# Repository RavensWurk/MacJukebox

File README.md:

This project is an effort to develop a jukebox expansion board for vintage Macintosh computers. 
It is meant to plug into the standard modem port on all compacts (and later desktops), and provide
USB storage, audio output via a headphone jack, and a control interface for the computers. 

It will support MP3 files at most common bitrates and sample frequencies. The Macintosh, being
unable to actually decode modern music files or output high qualithy sound, will act as the command
and control interface for this external board. Playlists can be made, viewing artists/albums/songs, 
controlling mixer levels and volume, and the external board will handle all the decoding of the file,
outputting it to the audio jack.

This repo is organised in to two parts, the firmware for the board itself under "Board", and the Macintosh
software side under "MacApp".

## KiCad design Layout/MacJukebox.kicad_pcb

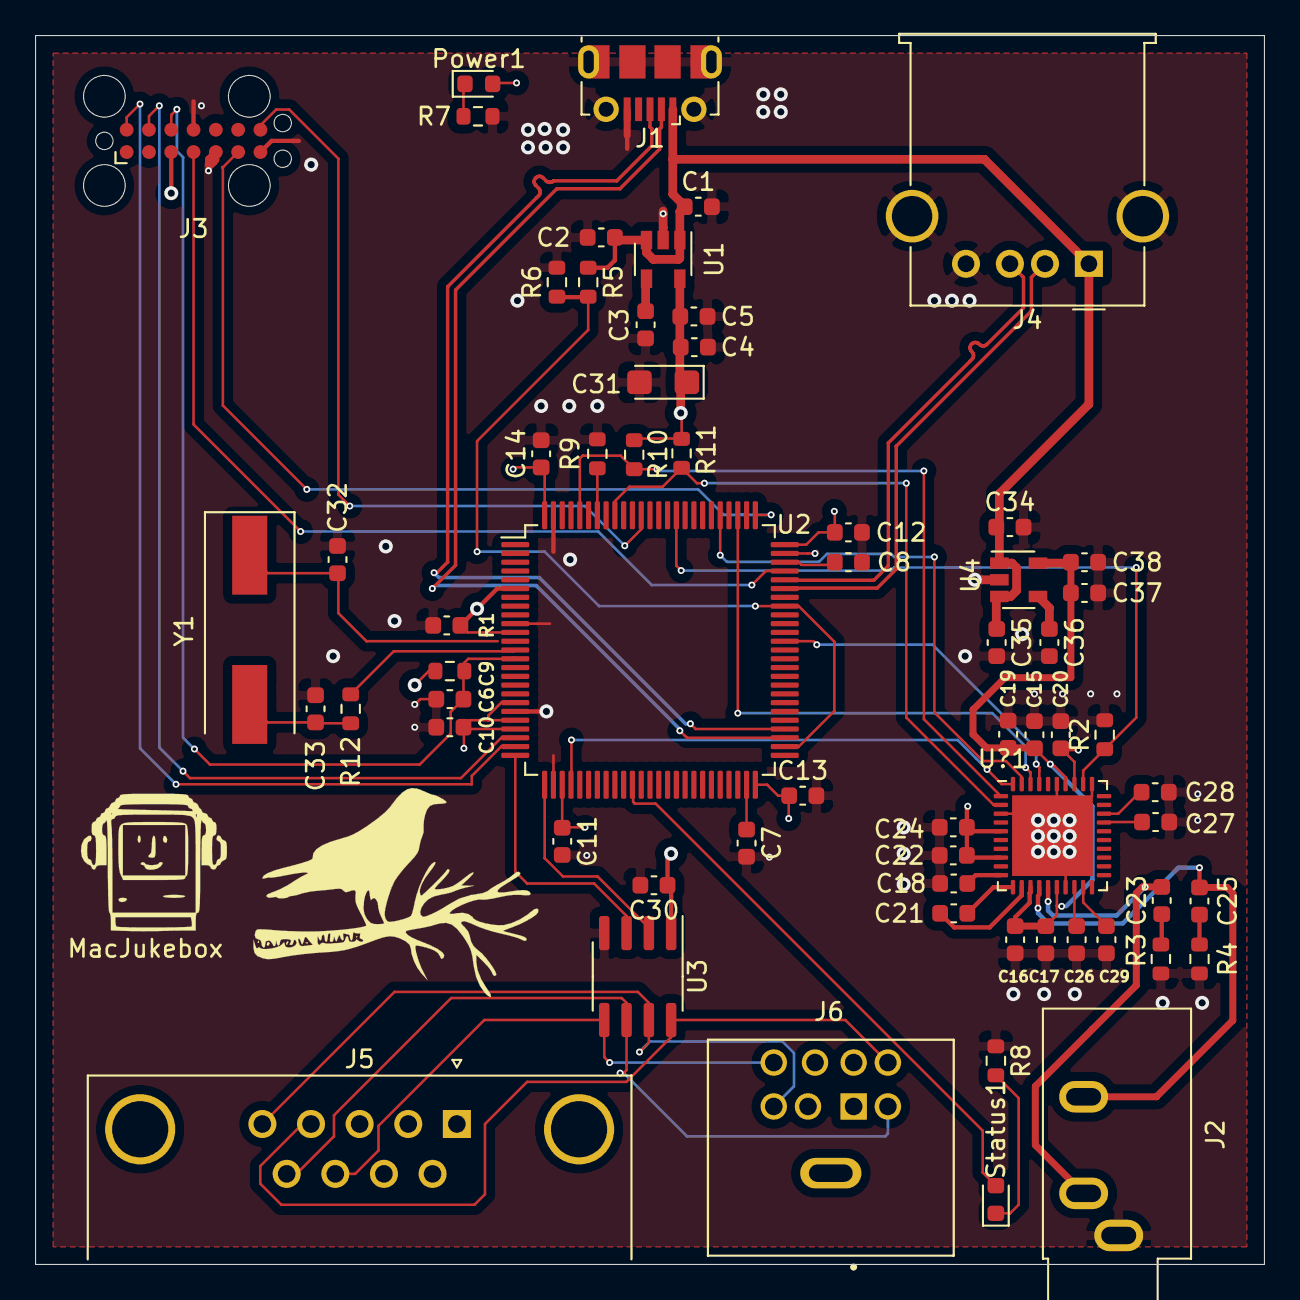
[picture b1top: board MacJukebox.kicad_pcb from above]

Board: 4 copper layers, 70.0 x 70.0 mm, 64 parts (0 on the bottom side), 50 nets.

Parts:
C1, C4, C19, C22, C24, C30, C34, C37: 1uF; C_0603_1608Metric
C2, C5, C6, C9, C10, C11, C12, C13, C14, C15, C16, C17, C20, C35, C38: 100nF; C_0603_1608Metric
C3, C36: 10nF; C_0603_1608Metric
C7, C8: 2.2uF; C_0603_1608Metric
C18, C21, C26, C29: 1uF (X7R); C_0603_1608Metric
C23, C25: 22nF; C_0603_1608Metric
C27, C28: 150pF (C0G); C_0603_1608Metric
C31: 10uF; CP_EIA-3216-18_Kemet-A
C32, C33: 18pF; C_0603_1608Metric
J1: USB_B_Micro; USB_Micro-B_Molex-105017-0001
J2: AudioJack3; Jack_3.5mm_CUI_SJ1-3533NG_Horizontal
J3: Conn_ST_STDC14; Tag-Connect_TC2070-IDC-FP_2x07_P1.27mm_Vertical
J4: USB_A; USB_A_Molex_67643_Horizontal
J5: Mac 128/512; DSUB-9_Female_Horizontal_P2.77x2.84mm_EdgePinOffset4.94mm_H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
J6: Mini-DIN-8; CUI_MD-80S
Power1: RED LED; LED_0603_1608Metric
R1: 100K; R_0603_1608Metric
R2, R9: 10K; R_0603_1608Metric
R3, R4: 51; R_0603_1608Metric
R5: 1K; R_0603_1608Metric
R6: 2.4K; R_0603_1608Metric
R7, R8: 200; R_0603_1608Metric
R10, R11: 4.7K; R_0603_1608Metric
R12: 1.1K; R_0603_1608Metric
Status1: GREEN LED; LED_0603_1608Metric
U1: LD3985M33R_SOT23; SOT-23-5
U2: STM32F407VGTx; LQFP-100_14x14mm_P0.5mm
U3: MAX3488; SOIC-8_3.9x4.9mm_P1.27mm
U4: LD3985M25R_SOT23; SOT-23-5
U?1: CS43L22; QFN-40-1EP_6x6mm_P0.5mm_EP4.6x4.6mm
Y1: Crystal; Crystal_SMD_HC49-SD

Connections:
+2V5: C15.1, C16.1, C17.1, C19.1, C37.1, C38.1, U4.5, U?1.13, U?1.16, U?1.34
+3V3: C4.1, C5.1, C9.1, C10.1, C11.1, C12.1, C13.1, C14.1, C20.1, C22.1, C24.1, C30.1, C31.1, J3.3, Power1.2, R1.1, R10.1, R11.1, U1.5, U2.6, U2.11, U2.19, U2.21, U2.22, U2.28, U2.50, U2.75, U2.100, U3.1, U?1.5, U?1.8, U?1.33
+5V: C1.1, C2.1, C34.1, C35.1, J1.1, J4.1, R5.1, U1.1, U1.3, U4.1, U4.3
DI: U2.25, U3.3
GND: C1.2, C2.2, C3.2, C4.2, C5.2, C6.2, C7.2, C8.2, C9.2, C10.2, C11.2, C12.2, C13.2, C14.2, C15.2, C16.2, C17.2, C18.2, C19.2, C20.2, C22.2, C24.2, C26.2, C27.2, C28.2, C29.2, C30.2, C31.2, C32.1, C33.1, C34.2, C35.2, C36.2, C37.2, C38.2, J1.5, J1.6, J2.S, J3.5, J3.7, J3.11, J4.4, J4.5, R2.2, R3.1, R4.1, R6.2, R7.2, R8.1, R9.1, U1.2, U2.10, U2.20, U2.27, U2.74, U2.99, U3.4, U4.2, U?1.3, U?1.17, U?1.31, U?1.35, U?1.41
unnamed: C3.1, U1.4
unnamed: C7.1, U2.49
unnamed: C8.1, U2.73
unnamed: C18.1, U?1.10
unnamed: C21.1, U?1.11
unnamed: C21.2, U?1.12
unnamed: C23.1, R3.2
unnamed: C23.2, J2.T, U?1.15
unnamed: C25.1, R4.2
unnamed: C25.2, J2.R, U?1.14
unnamed: C26.1, U?1.18
unnamed: C27.1, U?1.27
unnamed: C28.1, U?1.28
unnamed: C29.1, U?1.19
unnamed: C33.2, R12.1, Y1.2
unnamed: C36.1, U4.4
unnamed: Power1.1, R7.1
unnamed: R8.2, Status1.1
unnamed: R9.2, U2.94
PA4: U2.29, U?1.40
PB6: R11.2, U2.92, U?1.2
PB9: R10.2, U2.96, U?1.1
PC7: U2.64, U?1.37
PC10: U2.78, U?1.38
PC12: U2.80, U?1.39
PD4: R2.1, U2.85, U?1.32
PH0: C32.2, U2.12, Y1.1
PH1: R12.2, U2.13
RO: U2.26, U3.2
RS422_RX+: J5.4, J6.6, U3.8
RS422_RX-: J5.5, J6.3, U3.7
RS422_TX+: J5.8, J6.8, U3.5
RS422_TX-: J5.9, J6.5, U3.6
RST: C6.1, J3.12, R1.2, U2.14
STATUS_LED: Status1.2, U2.36
SWCLK: J3.6, U2.76
SWDIO: J3.4, U2.72
SWO: J3.8, U2.89
USB_COMPUTER_D+: J1.3, U2.54
USB_COMPUTER_D-: J1.2, U2.53
USB_STORAGE_D+: J4.3, U2.71
USB_STORAGE_D-: J4.2, U2.70
VBUS_SENSE: R5.2, R6.1, U2.52, U2.68
VCP_RX: J3.13, U2.23
VCP_TX: J3.14, U2.24

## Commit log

2021-03-11 Add working player with libmad
2021-03-13 Kick MP3 Player off to it's own task
2021-03-23 Bump I2S clock to 125MHz to fix error rate. Enable USART2
2021-03-23 Use own decoder loop to switch files at runtime
2021-04-02 Add libmad
2021-04-05 Add command interface, import ARMV7 patches
2021-08-03 Move to board folder, start mac app
2021-08-05 Fix endianness of length, set mac compatible baud
2021-08-07 Start integrating protobufs
2021-08-07 Use nanopb
2021-08-07 Create LICENSE
2021-08-07 Rework Makefile, add pause command
2021-08-07 Start adding file listings, add banner
2021-08-08 Add nanopb, add basic file listings command
2021-08-09 Start adding board schem and layout
2021-08-09 Add USB and LED sections
2021-08-10 Enable USB device, start laying out board
2021-08-11 Finish first layout of board
2021-08-13 Final corrections, submitted board to fab house
2021-08-13 Start trying out a proper window and menus
2021-08-16 Start laying out basic UI, add new commands
2021-08-17 Start adding list element
2021-08-18 Add port options, make list selectable
2021-08-19 Start adding basic protobuf handling for file list
